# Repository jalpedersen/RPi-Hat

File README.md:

% RPi B+ Hat

Raspberry Pi B+ Hat
============================

Expansion Board
----------------------------

This is a project template for a 
[Raspberry Pi B+ Hat](https://github.com/raspberrypi/hats).

This is based on work of [xesscorp](https://github.com/xesscorp/RPi_Hat_Template)

This version includes a CAT24C32 EEPROM for ID EEPROM as well as DS1340 RTC for
keeping track of time.

All headers (except ID_SC and ID_SD) are brought out into a separate header for
easy access. Also two small prototyping areas are provided

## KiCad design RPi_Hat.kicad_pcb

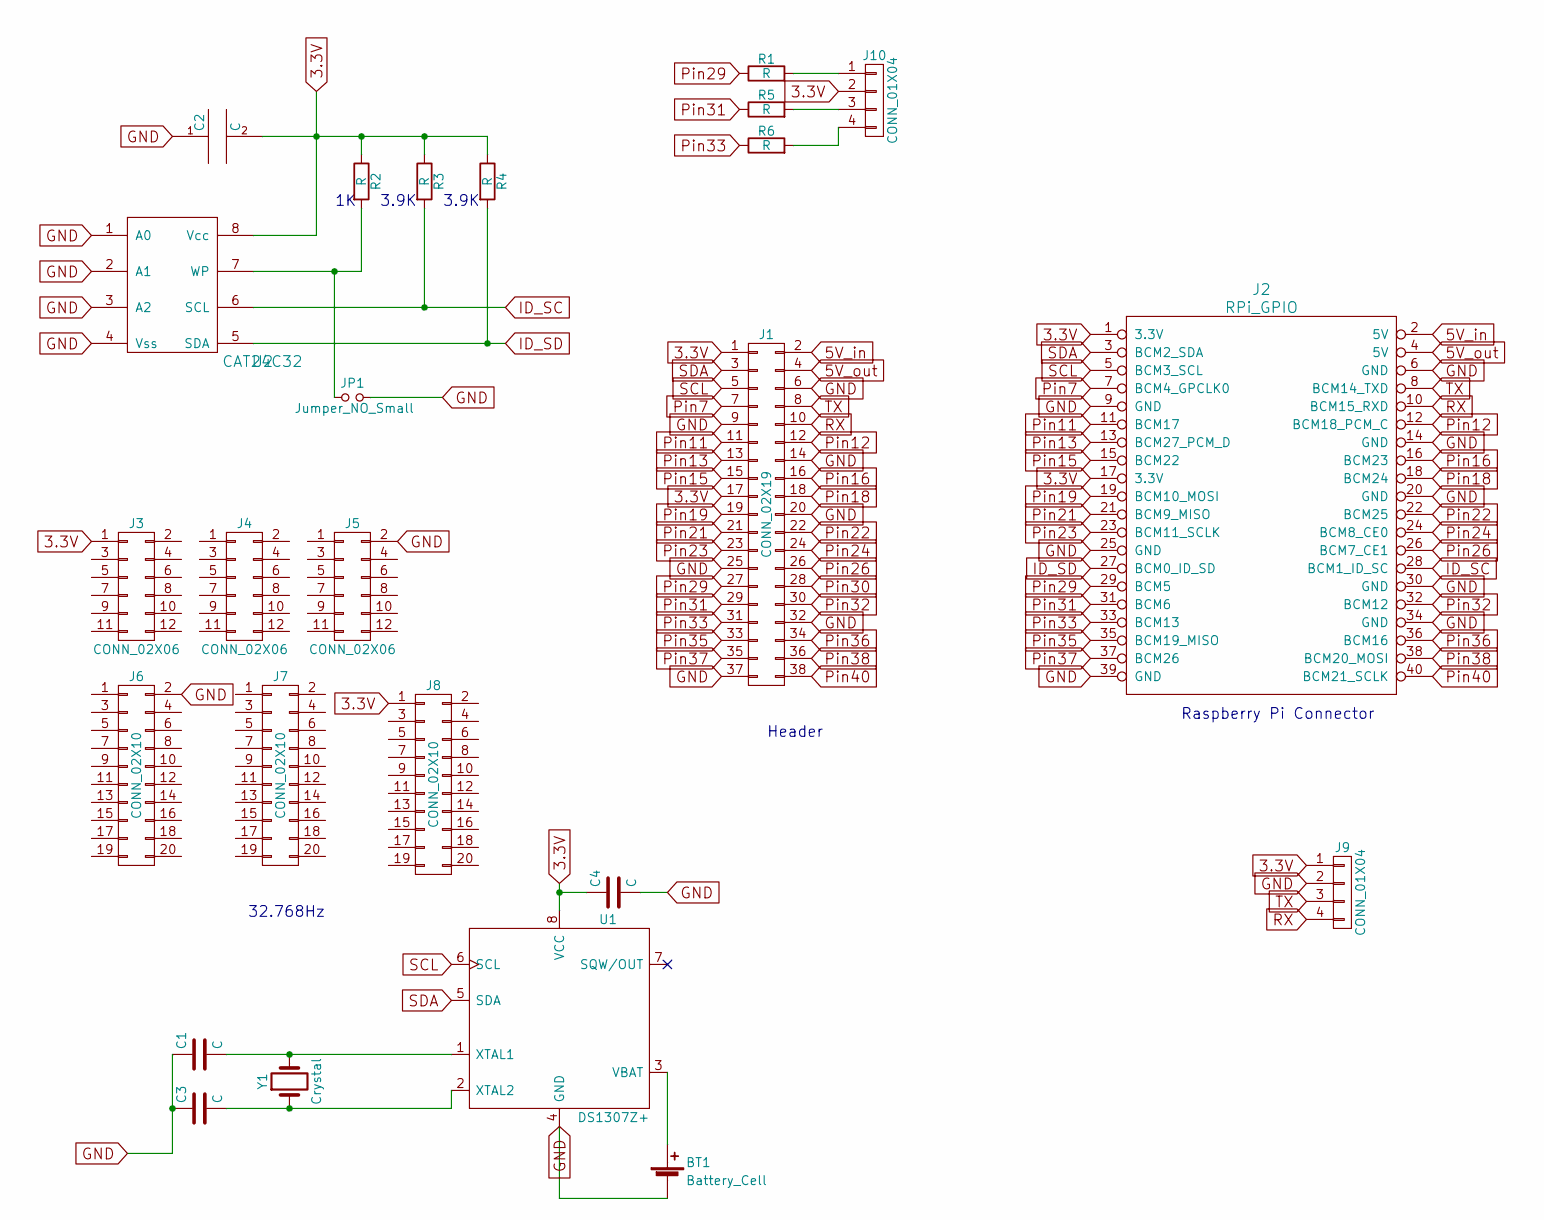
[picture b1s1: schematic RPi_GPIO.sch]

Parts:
BT1: Battery_Cell; Keystone_1058_1x2032-CoinCell
C1, C2, C3, C4: C; C_0805_HandSoldering
J1: CONN_02X19; Pin_Header_Straight_2x19_Pitch2.54mm
J2: RPi_GPIO; Pin_Header_Straight_2x20_Pitch2.54mm
J3, J4, J5: CONN_02X06; Pin_Header_Straight_2x06_Pitch2.54mm
J6, J7, J8: CONN_02X10; Pin_Header_Straight_2x10_Pitch2.54mm
J9: CONN_01X04; Pin_Header_Straight_1x04_Pitch2.54mm
J10: CONN_01X04; Pin_Header_Straight_1x04_Pitch1.27mm
JP1: Jumper_NO_Small; Pin_Header_Straight_2x01_Pitch2.54mm
R1, R2, R3, R4, R5, R6: R; R_0805_HandSoldering
U1: DS1307Z+; SOIC-8-N
U2: CAT24C32; SOIC-8-N
Y1: Crystal; Crystal_SMD_EuroQuartz_EQ161-2pin_3.2x1.5mm_HandSoldering

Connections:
3.3V: C2.2, C4.1, J1.1, J1.17, J2.1 (3.3V), J2.17 (3.3V), J3.1, J8.1, J9.1, J10.2, R2.1, R3.1, R4.1, U1.8 (VCC), U2.8 (Vcc)
5V_in: J1.2, J2.2 (5V)
5V_out: J1.4, J2.4 (5V)
GND: BT1.2 (-), C1.1, C2.1, C3.1, C4.2, J1.6, J1.9, J1.14, J1.20, J1.25, J1.32, J1.37, J2.6 (GND), J2.9 (GND), J2.14 (GND), J2.20 (GND), J2.25 (GND), J2.30 (GND), J2.34 (GND), J2.39 (GND), J5.2, J6.2, J9.2, JP1.2, U1.4 (GND), U2.1 (A0), U2.2 (A1), U2.3 (A2), U2.4 (Vss)
ID_SC: J2.28 (BCM1_ID_SC), R3.2, U2.6 (SCL)
ID_SD: J2.27 (BCM0_ID_SD), R4.2, U2.5 (SDA)
unnamed: BT1.1 (+), U1.3 (VBAT)
unnamed: C1.2, U1.1 (XTAL1), Y1.2
unnamed: C3.2, U1.2 (XTAL2), Y1.1
unnamed: J10.1, R1.2
unnamed: J10.3, R5.2
unnamed: J10.4, R6.2
unnamed: JP1.1, R2.2, U2.7 (WP)
Pin7: J1.7, J2.7 (BCM4_GPCLK0)
Pin11: J1.11, J2.11 (BCM17)
Pin12: J1.12, J2.12 (BCM18_PCM_C)
Pin13: J1.13, J2.13 (BCM27_PCM_D)
Pin15: J1.15, J2.15 (BCM22)
Pin16: J1.16, J2.16 (BCM23)
Pin18: J1.18, J2.18 (BCM24)
Pin19: J1.19, J2.19 (BCM10_MOSI)
Pin21: J1.21, J2.21 (BCM9_MISO)
Pin22: J1.22, J2.22 (BCM25)
Pin23: J1.23, J2.23 (BCM11_SCLK)
Pin24: J1.24, J2.24 (BCM8_CE0)
Pin26: J1.26, J2.26 (BCM7_CE1)
Pin29: J1.27, J2.29 (BCM5), R1.1
Pin30: J1.28
Pin31: J1.29, J2.31 (BCM6), R5.1
Pin32: J1.30, J2.32 (BCM12)
Pin33: J1.31, J2.33 (BCM13), R6.1
Pin35: J1.33, J2.35 (BCM19_MISO)
Pin36: J1.34, J2.36 (BCM16)
Pin37: J1.35, J2.37 (BCM26)
Pin38: J1.36, J2.38 (BCM20_MOSI)
Pin40: J1.38, J2.40 (BCM21_SCLK)
RX: J1.10, J2.10 (BCM15_RXD), J9.4
SCL: J1.5, J2.5 (BCM3_SCL), U1.6 (SCL)
SDA: J1.3, J2.3 (BCM2_SDA), U1.5 (SDA)
TX: J1.8, J2.8 (BCM14_TXD), J9.3

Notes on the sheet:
Header
Raspberry Pi Connector
32.768Hz
3.9K

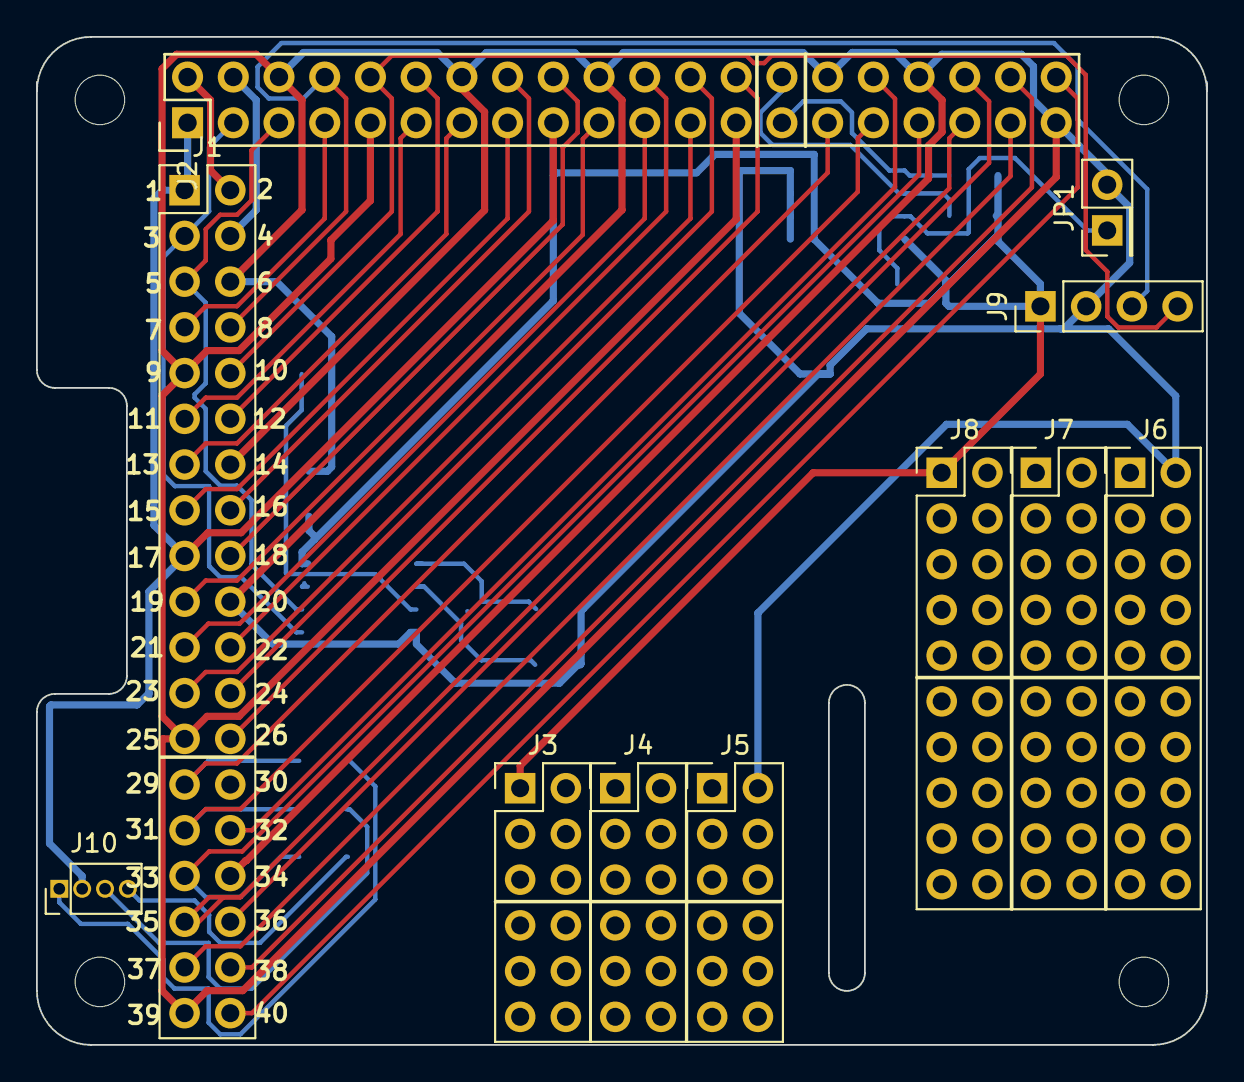
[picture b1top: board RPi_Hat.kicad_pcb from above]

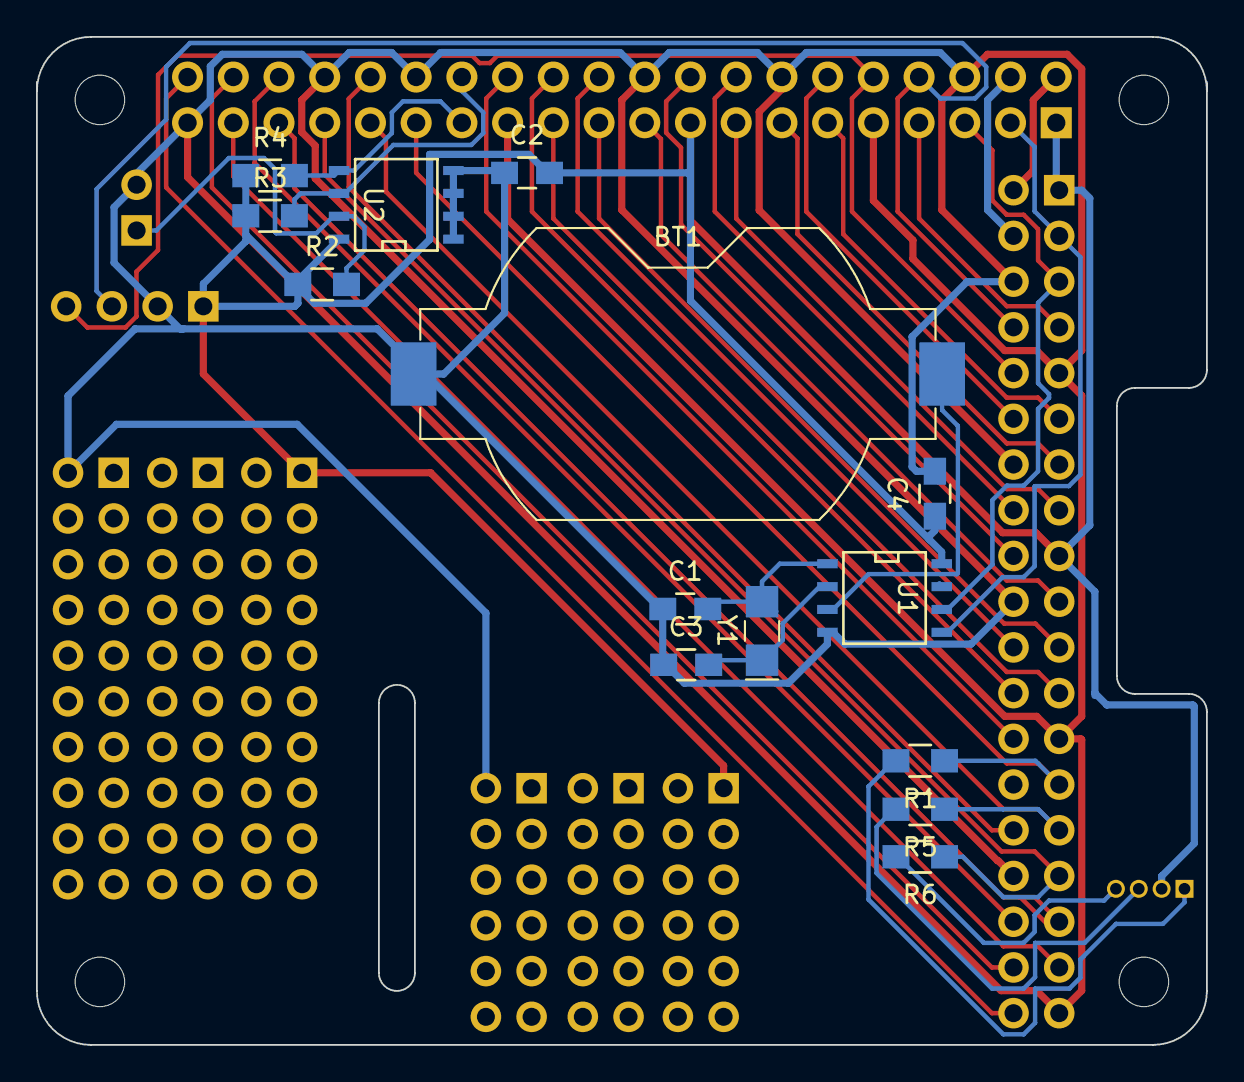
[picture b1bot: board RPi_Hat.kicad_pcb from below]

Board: 2 copper layers, 65.0 x 56.0 mm, 25 parts (14 on the bottom side), 39 nets.

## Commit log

2017-08-11 remove backup files
2017-08-11 typo in README
2017-08-14 cleanup and add RX/TX header
2017-08-15 support MCP7940N as well as ds1338/ds1340
2017-08-15 add room for an rgb led
2017-08-15 use connector footprint for LED as the standard one violated the DRC
2017-08-16 move LED to front and make sure there is enough clearance between components
2017-08-16 support SMD RGB LED as well
2017-08-16 remove SMD LED
2017-08-16 commit updated gerber.zip
